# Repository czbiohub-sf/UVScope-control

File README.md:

# UVScope-control
UVScope control software

## Intro
Thanks for visiting UVScope-control! Feel free to comment and make PRs in a constructive manner to help improve this project. Although it's been used to acquire hundreds of thousands of images (without errors) as part of dozens of multi-dimensional (MD) image acquisition experiments, it's likely that many bugs still exist because this software has only been tested in very narrow operating conditions, by only one user. 

UVScope-control was written to control a custom ultraviolet microscope built at Chan Zuckerberg Biohub, but could be adapted to control other microscopes by replacing device-specific hardware drivers. The microscope has a main control class, but works together with other modules to control a camera, XY stage, focus stage, and multiplexed LEDs with hardware sync module. A multi-dimensional image storage and processing class, MDImage, ingests images from the microscope, saving them to disk and/or memory in real time, in a format that can easily be re-loaded later into memory. MDImage also has a 6D image viewer built-in for quickly browsing image data.

Link to our published manuscript: https://journals.plos.org/ploscompbiol/article?id=10.1371/journal.pcbi.1009257

## Modules

### UVScope
- Orchestrates hardware drivers
- Implements:
  - A GUI for user control
  - Manual image snapping and previewing via Matlab's Image Acquisition toolbox
  - A 'runMDA' method that allows it to be driven by an external object implementing a MD acquisition
  - Active focus tracking over time, and across large areas of a sample.
  #### 

### MDEngine
- Runs a simple state machine
- Keeps track of MD acquisition parameters 
- Sends commands to UVScope for MD image acquisitions (XY positions, Z-position (offsets), Z-stacks, Channels, Time points)
- Feeds images to an MDImage object

### MDImage
- I/O for large imaging datasets
- Manipulation of 6D imaging datasets
- Implements the following image processing operations on large 6D datasets:
  - Digital re-focusing
  - Image stack alignment via cross-correlation
  - Timeseries drift correction via cross-correlation
  - Full transport of intensity (TIE) solver with non-uniform illumination
  - Richardson-Lucy image deconvolution (3D)
  - Flatfield illumination correction
  - Image registration between channels (affine transformation)
  
## How it works

## Microscope wiring diagram

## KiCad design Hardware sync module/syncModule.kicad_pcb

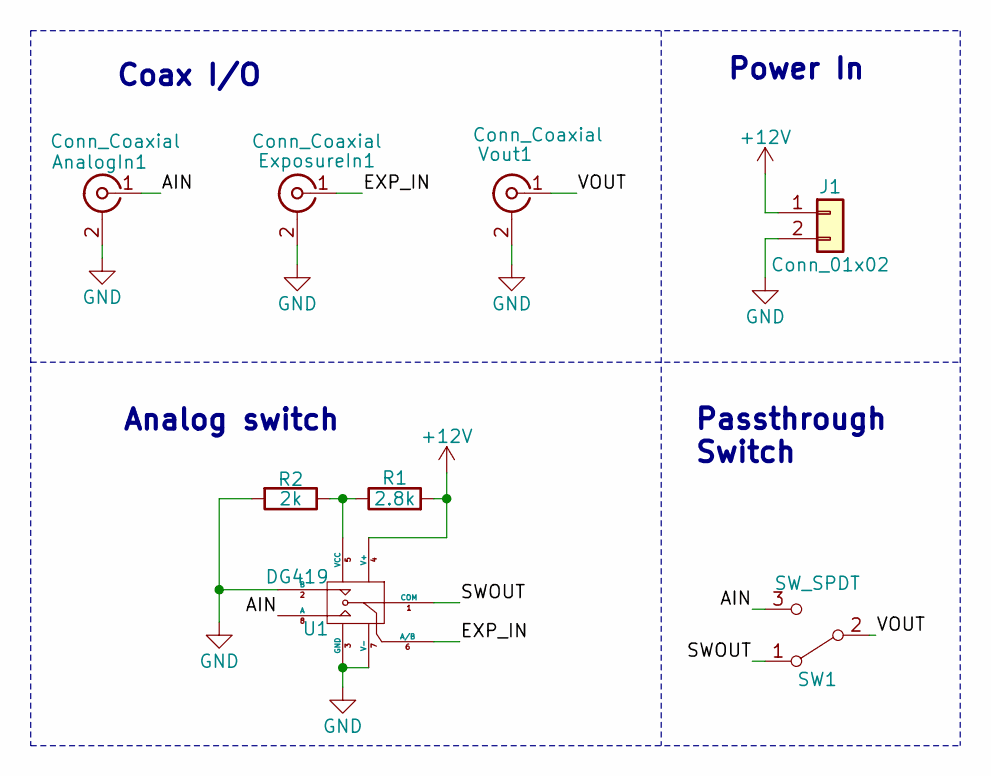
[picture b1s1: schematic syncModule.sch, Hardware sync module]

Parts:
AnalogIn1: Conn_Coaxial; Molex_MicroLatch-53253-0270_02x2.00mm_Straight
ExposureIn1: Conn_Coaxial; Molex_MicroLatch-53253-0270_02x2.00mm_Straight
J1: Conn_01x02; Molex_MicroLatch-53253-0270_02x2.00mm_Straight
R1: 2.8k; R_Axial_DIN0309_L9.0mm_D3.2mm_P12.70mm_Horizontal
R2: 2k; R_Axial_DIN0309_L9.0mm_D3.2mm_P12.70mm_Horizontal
SW1: SW_SPDT; Molex_MicroLatch-53253-0370_03x2.00mm_Straight
U1: DG419; DIP-8_W7.62mm
Vout1: Conn_Coaxial; Molex_MicroLatch-53253-0270_02x2.00mm_Straight

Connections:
+12V: J1.1, R1.2, U1.4 (V+)
/AIN: AnalogIn1.1 (In), SW1.3 (C), U1.8 (A)
/EXP_IN: ExposureIn1.1 (In), U1.6 (A/B)
/SWOUT: SW1.1 (A), U1.1 (COM)
/VOUT: SW1.2 (B), Vout1.1 (In)
GND: AnalogIn1.2 (Ext), ExposureIn1.2 (Ext), J1.2, R2.2, U1.2 (B), U1.3 (GND), U1.7 (V-), Vout1.2 (Ext)
unnamed: R1.1, R2.1, U1.5 (VCC)

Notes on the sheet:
Coax I/O
Power In
Analog switch
Passthrough Switch

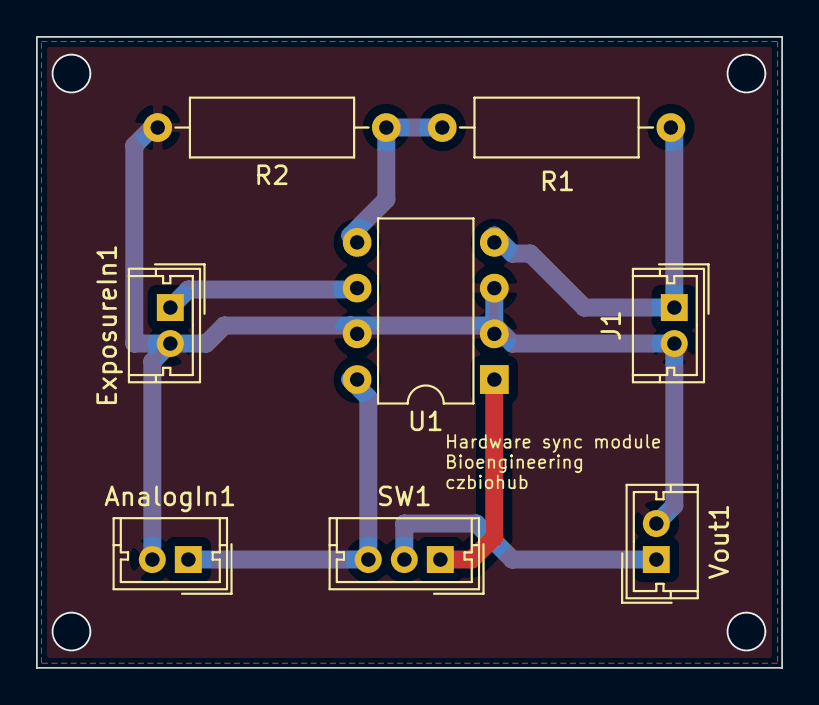
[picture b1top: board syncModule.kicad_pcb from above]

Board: 2 copper layers, 41.4 x 35.1 mm, 8 parts (0 on the bottom side), 7 nets.

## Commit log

2020-09-04 Initial commit for public repo
2020-09-08 Added electronics for hardware sync module, and some schematic images
2021-08-10 Update LICENSE
